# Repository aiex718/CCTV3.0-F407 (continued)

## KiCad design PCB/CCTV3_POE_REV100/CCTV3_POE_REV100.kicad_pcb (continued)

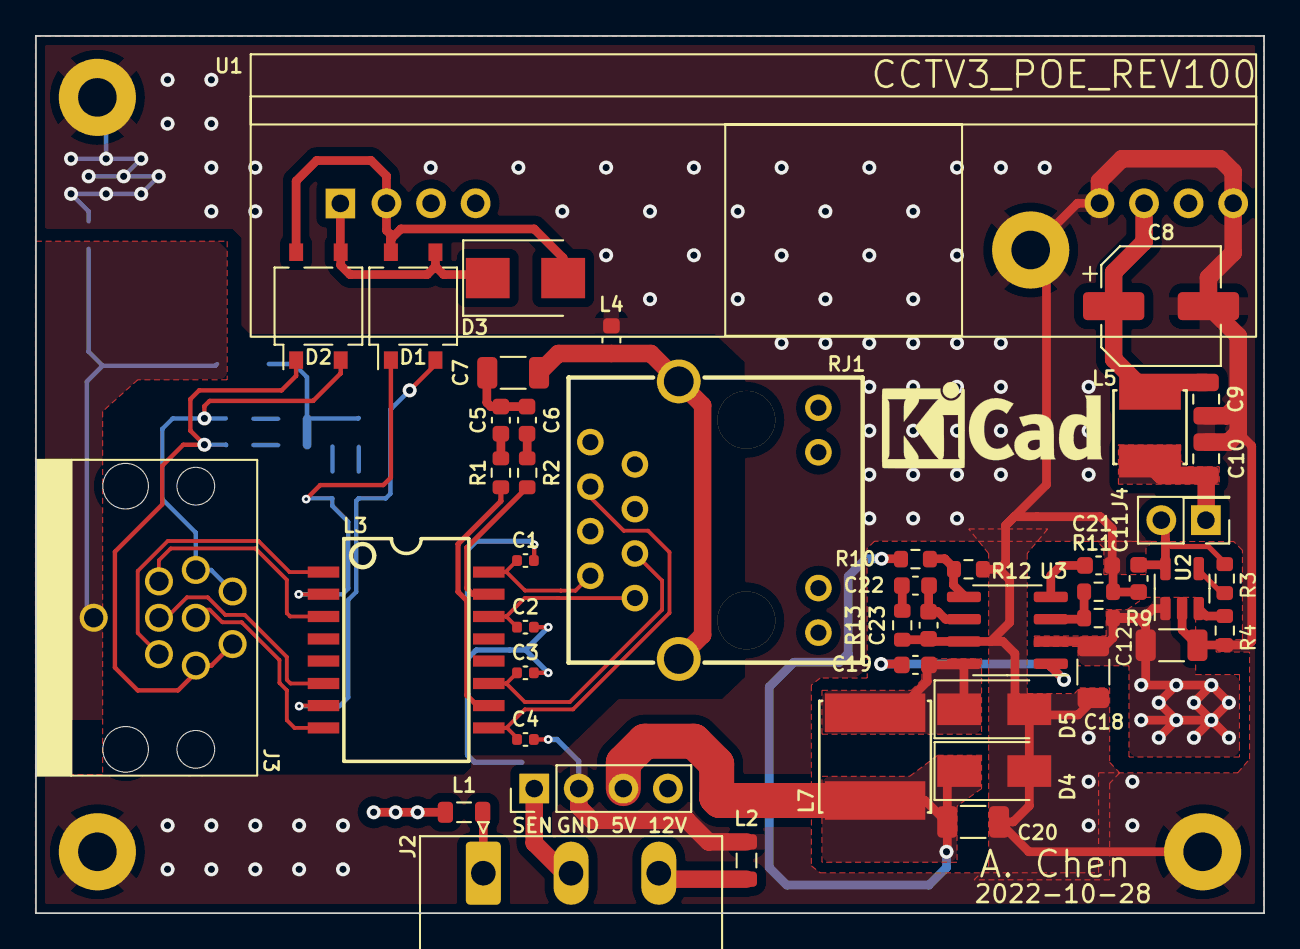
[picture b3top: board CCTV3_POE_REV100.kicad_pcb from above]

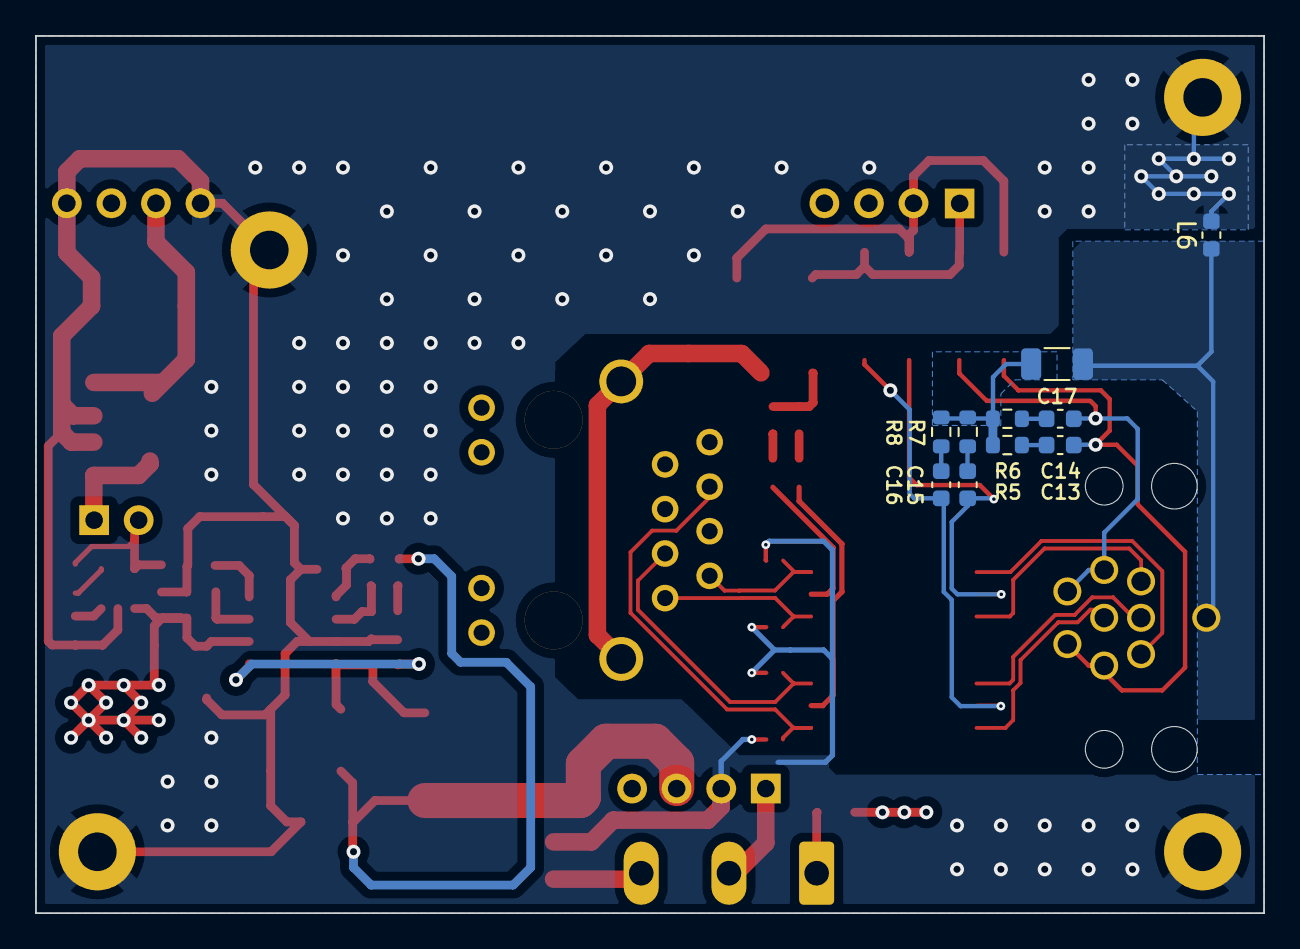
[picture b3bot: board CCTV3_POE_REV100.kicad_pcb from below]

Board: 4 copper layers, 70.0 x 50.0 mm, 60 parts (10 on the bottom side), 44 nets.

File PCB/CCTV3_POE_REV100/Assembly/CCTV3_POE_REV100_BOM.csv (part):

"Source:","/Users/aiex718/Private/Workspace/CCTV3.0-F407/PCB/CCTV3_POE_REV100/CCTV3_POE_REV100.kicad_sch"
"Date:","Thursday, 24 November 2022 at 03:23:11"
"Tool:","Eeschema (6.0.8-1)-1"
"Generator:","/Applications/KiCad/KiCad.app/Contents/SharedSupport/plugins/bom_csv_grouped_by_value.py"
"Component Count:","60"

"Individual Components:"

"Item","Qty","Reference(s)","Value","LibPart","Footprint","Datasheet","JLC Part","LCSC Part","Manufacturer","Model","Voltage"
"","","C1","10pF","lcsc_parts:Cap","Capacitor_SMD:C_0402_1005Metric","~","","TBD","","","50V"
"","","C2","10pF","lcsc_parts:Cap","Capacitor_SMD:C_0402_1005Metric","~","","TBD","","","50V"
"","","C3","10pF","lcsc_parts:Cap","Capacitor_SMD:C_0402_1005Metric","~","","TBD","","","50V"
"","","C4","10pF","lcsc_parts:Cap","Capacitor_SMD:C_0402_1005Metric","~","","TBD","","","50V"
"","","C5","10nF","lcsc_parts:Cap","Capacitor_SMD:C_0603_1608Metric","~","","TBD","","","250V"
"","","C6","10nF","lcsc_parts:Cap","Capacitor_SMD:C_0603_1608Metric","~","","TBD","","","250V"
"","","C7","1000pF","lcsc_parts:Cap","Capacitor_SMD:C_1206_3216Metric","~","","TBD","","","2KV"
"","","C8","220uF","lcsc_parts:Cap_Polarized","Capacitor_SMD:CP_Elec_6.3x7.7","https://lcsc.com/product-detail/Others_Lelon-VZT221M1ETR-060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","Extended Part","C371974","Lelon","","25V"
"","","C9","10uF","lcsc_parts:Cap","Capacitor_SMD:C_0805_2012Metric","~","","TBD","","","25V"
"","","C10","10uF","lcsc_parts:Cap","Capacitor_SMD:C_0805_2012Metric","~","","TBD","","","25V"
"","","C11","10uF","lcsc_parts:Cap","Capacitor_SMD:C_0603_1608Metric","~","","TBD","","","25V"
"","","C12","10uF","lcsc_parts:Cap","Capacitor_SMD:C_1206_3216Metric","~","","TBD","","","50V"
"","","C13","10nF","lcsc_parts:Cap","Capacitor_SMD:C_0603_1608Metric","~","","TBD","","","250V"
"","","C14","10nF","lcsc_parts:Cap","Capacitor_SMD:C_0603_1608Metric","~","","TBD","","","250V"
"","","C15","10nF","lcsc_parts:Cap","Capacitor_SMD:C_0603_1608Metric","~","","TBD","","","250V"
"","","C16","10nF","lcsc_parts:Cap","Capacitor_SMD:C_0603_1608Metric","~","","TBD","","","250V"
"","","C17","1000pF","lcsc_parts:Cap","Capacitor_SMD:C_1206_3216Metric","~","","TBD","","","2KV"
"","","C18","10uF","lcsc_parts:Cap","Capacitor_SMD:C_1206_3216Metric","~","","TBD","","","50V"
"","","C19","100nF","lcsc_parts:Cap","Capacitor_SMD:C_0603_1608Metric","~","","TBD","","","50V"
"","","C20","47uF","lcsc_parts:Cap","Capacitor_SMD:C_1206_3216Metric","~","","TBD","","","10V"
"","","C21","10nF","lcsc_parts:Cap","Capacitor_SMD:C_0603_1608Metric","~","","TBD","","","50"
"","","C22","1nF","lcsc_parts:Cap","Capacitor_SMD:C_0603_1608Metric","~","","TBD","","","50V"
"","","C23","47pF","lcsc_parts:Cap","Capacitor_SMD:C_0603_1608Metric","~","","TBD","","","50V"
"","","D1","MB6S","Diode_Bridge:MB6S","Package_TO_SOT_SMD:TO-269AA","http://www.vishay.com/docs/88573/dfs.pdf","","","","",""
"","","D2","MB6S","Diode_Bridge:MB6S","Package_TO_SOT_SMD:TO-269AA","http://www.vishay.com/docs/88573/dfs.pdf","","","","",""
"","","D3","SMBJ58A","lcsc_parts:SMBJ58A_C707476","Diode_SMD:D_SMB","https://lcsc.com/product-detail/TVS_FTR-SMBJ58A_C707476.html","Extended Part","C707476","FTR","",""
"","","D4","SMAJ5.0CA","lcsc_parts:SMAJ5.0CA-C83324","Diode_SMD:D_SMA","https://lcsc.com/product-detail/TVS_Littelfuse_SMAJ5-0CA_SMA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","Extended Part","C83324","Littelfuse","",""
"","","D5","SS34","lcsc_parts:SS34","Diode_SMD:D_SMA","https://lcsc.com/product-detail/Schottky-Barrier-Diodes-SBD_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","Basic Part","C8678","MDD","",""
"","","H1","MountingHole","Mechanical:MountingHole_Pad","MountingHole:MountingHole_2.2mm_M2_Pad","~","","","","",""
"","","H2","MountingHole","Mechanical:MountingHole_Pad","MountingHole:MountingHole_2.2mm_M2_Pad","~","","","","",""
"","","H3","MountingHole","Mechanical:MountingHole_Pad","MountingHole:MountingHole_2.2mm_M2_Pad","~","","","","",""
"","","H4","MountingHole","Mechanical:MountingHole_Pad","MountingHole:MountingHole_2.2mm_M2_Pad","~","","","","",""
"","","J1","Conn_01x04","Connector_Generic:Conn_01x04","Connector_PinHeader_2.54mm:PinHeader_1x04_P2.54mm_Vertical","~","","","","",""
"","","J2","Conn_4-20mA","Connector_Generic:Conn_01x03","Connector_Phoenix_MSTB:PhoenixContact_MSTBA_2,5_3-G_1x03_P5.00mm_Horizontal","~","","","","",""
"","","J3","M12_8P_Horizontal","CCTV3_POE:M12_8P_Horizontal","CCTV3_POE:M12_8P_Horizontal","https://item.taobao.com/item.htm?spm=a230r.1.14.231.1cd43c38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","","","","",""
"","","J4","Jmp_12V","Connector_Generic:Conn_01x02","Connector_PinHeader_2.54mm:PinHeader_2x01_P2.54mm_Vertical","~","","","","",""
"","","L1","100R","lcsc_parts:GZ1608D601TF","Inductor_SMD:L_0805_2012Metric","https://lcsc.com/product-detail/Ferrite-Beads-And-Chips_600R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","Basic Part","C1015","Sunlord","GZ2012D101TF",""
"","","L2","100R","lcsc_parts:GZ1608D601TF","Inductor_SMD:L_0805_2012Metric","https://lcsc.com/product-detail/Ferrite-Beads-And-Chips_600R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","Basic Part","C1015","Sunlord","GZ2012D101TF",""
"","","L3","HY601742","lcsc_parts:HY601742","lcsc_parts:RJ45-SMD_HY601742","https://lcsc.com/product-detail/RJ45-Transformer_100MNetwork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","Extended Part","C55684","HANRUN","",""
"","","L4","600R","lcsc_parts:GZ1608D601TF","Inductor_SMD:L_0603_1608Metric","https://lcsc.com/product-detail/Ferrite-Beads-And-Chips_600R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","Basic Part","C1002","Sunlord","GZ1608D601TF",""
"","","L5","SMNR4020-2.2UH","lcsc_parts:SMNR4020-2.2UH","lcsc_parts:IND-SMD_L4.0-W4.0_SMNR4020","https://lcsc.com/product-detail/Power-Inductors_2-2uH-20_C13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","Extended Part","C135262","SXN","",""
"","","L6","600R","lcsc_parts:GZ1608D601TF","Inductor_SMD:L_0603_1608Metric","https://lcsc.com/product-detail/Ferrite-Beads-And-Chips_600R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","Basic Part","C1002","Sunlord","GZ1608D601TF",""
"","","L7","33uH","lcsc_parts:LVS606045-330M-N","lcsc_parts:IND-SMD_L6.0-W6.0","https://lcsc.com/product-detail/Power-Inductors_Chilisin-Ele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","","C285825","Chilisin Elec","",""
"","","R1","75R","lcsc_parts:Res","Resistor_SMD:R_0603_1608Metric","~","","TBD","","",""
"","","R2","75R","lcsc_parts:Res","Resistor_SMD:R_0603_1608Metric","~","","TBD","","",""
"","","R3","4.7k","lcsc_parts:Res","Resistor_SMD:R_0603_1608Metric","~","","TBD","","",""
"","","R4","6.8k","lcsc_parts:Res","Resistor_SMD:R_0603_1608Metric","~","","TBD","","",""
"","","R5","75R","lcsc_parts:Res","Resistor_SMD:R_0603_1608Metric","~","","TBD","","",""
"","","R6","75R","lcsc_parts:Res","Resistor_SMD:R_0603_1608Metric","~","","TBD","","",""
"","","R7","75R","lcsc_parts:Res","Resistor_SMD:R_0603_1608Metric","~","","TBD","","",""
"","","R8","75R","lcsc_parts:Res","Resistor_SMD:R_0603_1608Metric","~","","TBD","","",""
"","","R9","330k","lcsc_parts:Res","Resistor_SMD:R_0603_1608Metric","~","","TBD","","",""
"","","R10","10k","lcsc_parts:Res","Resistor_SMD:R_0603_1608Metric","~","","TBD","","",""
"","","R11","68k","lcsc_parts:Res","Resistor_SMD:R_0603_1608Metric","~","","TBD","","",""
"","","R12","2k","lcsc_parts:Res","Resistor_SMD:R_0603_1608Metric","~","","TBD","","",""
"","","R13","30K","lcsc_parts:Res","Resistor_SMD:R_0603_1608Metric","~","","TBD","","",""
"","","RJ1","R-RJ45S08P-C000","lcsc_parts:R-RJ45S08P-C000","lcsc_parts:RJ45-TH_R-RJ45S08P-C000","https://lcsc.com/product-detail/Ethernet-Connectors-Modular-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","Extended Part","C386764","Shenzhen Cankemeng","",""
"","","U1","DP5312_SDAPO","CCTV3_POE:DP5312_SDAPO","CCTV3_POE:DP5312_SDAPO","","","","","",""
"","","U2","MT9700","lcsc_parts:MT9700","Package_TO_SOT_SMD:SOT-23-5","https://lcsc.com/product-detail/PMIC-Power-Distribution-Swit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","Extended Part","C89855","AEROSEMI","",""
"","","U3","TPS54331DR","lcsc_parts:TPS54331DR","Package_SO:SOIC-8_3.9x4.9mm_P1.27mm","https://lcsc.com/product-detail/DC-DC-Converters_TI_TPS54331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","Basic Part","C9865","TI","",""



"Collated Components:"

"Item","Qty","Reference(s)","Value","LibPart","Footprint","Datasheet","JLC Part","LCSC Part","Manufacturer","Model","Voltage"
"1","4","C1, C2, C3, C4","10pF","lcsc_parts:Cap","Capacitor_SMD:C_0402_1005Metric","~","","TBD","","","50V"
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
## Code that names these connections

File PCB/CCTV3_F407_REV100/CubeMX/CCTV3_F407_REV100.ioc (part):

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Mcu.Name=STM32F407Z(E-G)Tx
Mcu.Package=LQFP144
Mcu.UserName=STM32F407ZETx
PA0-WKUP.GPIOParameters=GPIO_Label
PA0-WKUP.GPIO_Label=BTN_WKUP
PA0-WKUP.Signal=GPIO_Input
PA1.Mode=RMII
PA1.Signal=ETH_REF_CLK
PA10.GPIOParameters=GPIO_Label
PA10.GPIO_Label=USB_OTG_FS_ID
PA10.Signal=GPIO_Output
PA11.Mode=Device_Only
PA11.Signal=USB_OTG_FS_DM
PA12.Mode=Device_Only
PA12.Signal=USB_OTG_FS_DP
PA13.Mode=JTAG_5_pins
PA13.Signal=SYS_JTMS-SWDIO
PA14.Mode=JTAG_5_pins
PA14.Signal=SYS_JTCK-SWCLK
PA15.Mode=JTAG_5_pins
PA15.Signal=SYS_JTDI
PA2.Mode=RMII
PA2.Signal=ETH_MDIO
PA3.Signal=ADCx_IN3
PA4.Mode=Slave_8_bits_External_Synchro
PA4.Signal=DCMI_HSYNC
PA6.Mode=Slave_8_bits_External_Synchro
PA6.Signal=DCMI_PIXCLK
PA7.Mode=RMII
PA7.Signal=ETH_CRS_DV
PA8.Mode=Clock-out-1
PA8.Signal=RCC_MCO_1
PA9.Mode=Slave_8_bits_External_Synchro
PA9.Signal=DCMI_D0
PB0.GPIOParameters=GPIO_Label
PB0.GPIO_Label=PWM_NC0
PB0.Signal=S_TIM3_CH3
PB1.GPIOParameters=GPIO_Label
PB1.GPIO_Label=PWM_NC1
PB1.Signal=S_TIM3_CH4
PB10.Mode=I2C
PB10.Signal=I2C2_SCL
PB11.Mode=I2C
PB11.Signal=I2C2_SDA
PB12.Mode=NSS_Signal_Hard_Input
PB12.Signal=SPI2_NSS
PB13.Mode=Full_Duplex_Master
PB13.Signal=SPI2_SCK
PB14.Mode=Full_Duplex_Master
PB14.Signal=SPI2_MISO
PB15.Mode=Full_Duplex_Master
PB15.Signal=SPI2_MOSI
PB2.GPIOParameters=GPIO_Label
PB2.GPIO_Label=BOOT1
PB2.Signal=GPIO_Input
PB3.Mode=JTAG_5_pins
PB3.Signal=SYS_JTDO-SWO
PB4.Mode=JTAG_5_pins
PB4.Signal=SYS_JTRST
PB5.GPIOParameters=GPIO_Label
PB5.GPIO_Label=PWM_NC2
PB5.Signal=S_TIM3_CH2
PB6.Mode=Slave_8_bits_External_Synchro
PB6.Signal=DCMI_D5
PB7.Mode=Slave_8_bits_External_Synchro
PB7.Signal=DCMI_VSYNC
PB8.GPIOParameters=GPIO_Label
PB8.GPIO_Label=SCCB_SCL
PB8.Mode=I2C
PB8.Signal=I2C1_SCL
PB9.GPIOParameters=GPIO_Label
PB9.GPIO_Label=SCCB_SDA
PB9.Mode=I2C
PB9.Signal=I2C1_SDA
PC1.Mode=RMII
PC1.Signal=ETH_MDC
PC10.Mode=Asynchronous
PC10.Signal=USART3_TX
PC11.Mode=Asynchronous
PC11.Signal=USART3_RX
PC12.Mode=Asynchronous
PC12.Signal=UART5_TX
PC13-ANTI_TAMP.GPIOParameters=GPIO_Label
PC13-ANTI_TAMP.GPIO_Label=BTN_TAMP
PC13-ANTI_TAMP.Signal=GPIO_Input
PC14-OSC32_IN.Mode=LSE-External-Oscillator
PC14-OSC32_IN.Signal=RCC_OSC32_IN
PC15-OSC32_OUT.Mode=LSE-External-Oscillator
PC15-OSC32_OUT.Signal=RCC_OSC32_OUT
PC4.Mode=RMII
PC4.Signal=ETH_RXD0
PC5.Mode=RMII
PC5.Signal=ETH_RXD1
PC6.GPIOParameters=GPIO_Label
PC6.GPIO_Label=PWM_NC3
PC6.Signal=S_TIM3_CH1
PC7.Mode=Slave_8_bits_External_Synchro
PC7.Signal=DCMI_D1
PC8.Mode=Slave_8_bits_External_Synchro
PC8.Signal=DCMI_D2
PC9.Mode=Slave_8_bits_External_Synchro
PC9.Signal=DCMI_D3
PD0.Signal=FSMC_D2_DA2
PD1.Signal=FSMC_D3_DA3
PD10.Signal=FSMC_D15_DA15
PD11.Signal=FSMC_A16_CLE
PD12.Signal=FSMC_A17_ALE
PD14.Signal=FSMC_D0_DA0
PD15.Signal=FSMC_D1_DA1
PD2.Mode=Asynchronous
PD2.Signal=UART5_RX
PD4.Signal=FSMC_NOE
PD5.Signal=FSMC_NWE
PD8.Signal=FSMC_D13_DA13
PD9.Signal=FSMC_D14_DA14
PE0.Signal=FSMC_NBL0
PE1.Signal=FSMC_NBL1
PE10.Signal=FSMC_D7_DA7
PE11.Signal=FSMC_D8_DA8
PE12.Signal=FSMC_D9_DA9
PE13.Signal=FSMC_D10_DA10
PE14.Signal=FSMC_D11_DA11
PE15.Signal=FSMC_D12_DA12
PE2.GPIOParameters=GPIO_Label
PE2.GPIO_Label=OV_PWDN
PE2.Signal=GPIO_Output
PE3.GPIOParameters=GPIO_Label
PE3.GPIO_Label=OV_RESET
PE3.Signal=GPIO_Output
PE4.Mode=Slave_8_bits_External_Synchro
PE4.Signal=DCMI_D4
PE5.Mode=Slave_8_bits_External_Synchro
PE5.Signal=DCMI_D6
PE6.Mode=Slave_8_bits_External_Synchro
PE6.Signal=DCMI_D7
PE7.Signal=FSMC_D4_DA4
PE8.Signal=FSMC_D5_DA5
PE9.Signal=FSMC_D6_DA6
PF0.Signal=FSMC_A0
PF1.Signal=FSMC_A1
PF11.GPIOParameters=GPIO_Label
PF11.GPIO_Label=LED_LINK
PF11.Signal=GPIO_Output
PF12.Signal=FSMC_A6
PF13.Signal=FSMC_A7
PF14.Signal=FSMC_A8
PF15.Signal=FSMC_A9
PF2.Signal=FSMC_A2
PF3.Signal=FSMC_A3
PF4.Signal=FSMC_A4
PF5.Signal=FSMC_A5
PF6.GPIOParameters=GPIO_Label
PF6.GPIO_Label=BUZZ_OUT
PF6.Signal=S_TIM10_CH1
PF7.GPIOParameters=GPIO_Label
PF7.GPIO_Label=LED_PWM_CH1
PF7.Signal=S_TIM11_CH1
PF8.GPIOParameters=GPIO_Label
PF8.GPIO_Label=LED_PWM_CH2
PF8.Signal=S_TIM13_CH1
PG0.Signal=FSMC_A10
PG1.Signal=FSMC_A11
PG11.Mode=RMII
PG11.Signal=ETH_TX_EN
PG12.Mode=NorPsramChipSelect4_1
PG12.Signal=FSMC_NE4
PG13.Mode=RMII
PG13.Signal=ETH_TXD0
PG14.Mode=RMII
PG14.Signal=ETH_TXD1
PG15.GPIOParameters=GPIO_Label
PG15.GPIO_Label=LED_STAT
PG15.Signal=GPIO_Output
PG2.Signal=FSMC_A12
PG3.Signal=FSMC_A13
PG4.Signal=FSMC_A14
PG5.Signal=FSMC_A15
PH0-OSC_IN.Mode=HSE-External-Oscillator
PH0-OSC_IN.Signal=RCC_OSC_IN
PH1-OSC_OUT.Mode=HSE-External-Oscillator
PH1-OSC_OUT.Signal=RCC_OSC_OUT
RCC.HSE_VALUE=25000000
RCC.SYSCLKFreq_VALUE=168000000
RCC.SYSCLKSource=RCC_SYSCLKSOURCE_PLLCLK
board=custom

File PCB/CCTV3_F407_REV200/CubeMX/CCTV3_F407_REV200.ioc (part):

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Mcu.Name=STM32F407V(E-G)Tx
Mcu.Package=LQFP100
Mcu.UserName=STM32F407VETx
PA0-WKUP.GPIOParameters=GPIO_Label
PA0-WKUP.GPIO_Label=BTN_WKUP
PA0-WKUP.Signal=GPIO_Input
PA1.Mode=RMII
PA1.Signal=ETH_REF_CLK
PA10.GPIOParameters=GPIO_Label
PA10.GPIO_Label=USB_OTG_FS_ID
PA10.Signal=GPIO_Input
PA11.Mode=Device_Only
PA11.Signal=USB_OTG_FS_DM
PA12.Mode=Device_Only
PA12.Signal=USB_OTG_FS_DP
PA13.Mode=Serial_Wire
PA13.Signal=SYS_JTMS-SWDIO
PA14.Mode=Serial_Wire
PA14.Signal=SYS_JTCK-SWCLK
PA15.GPIOParameters=GPIO_Label
PA15.GPIO_Label=W25_CS
PA15.Mode=NSS_Signal_Hard_Output
PA15.Signal=SPI3_NSS
PA2.Mode=RMII
PA2.Signal=ETH_MDIO
PA3.GPIOParameters=GPIO_Label
PA3.GPIO_Label=PWM_BUZZ
PA3.Signal=S_TIM9_CH2
PA4.Mode=Slave_8_bits_External_Synchro
PA4.Signal=DCMI_HSYNC
PA6.Mode=Slave_8_bits_External_Synchro
PA6.Signal=DCMI_PIXCLK
PA7.Mode=RMII
PA7.Signal=ETH_CRS_DV
PA8.Mode=Clock-out-1
PA8.Signal=RCC_MCO_1
PB11.Mode=RMII
PB11.Signal=ETH_TX_EN
PB12.Mode=RMII
PB12.Signal=ETH_TXD0
PB13.Mode=RMII
PB13.Signal=ETH_TXD1
PB14.GPIOParameters=GPIO_Label
PB14.GPIO_Label=PWM_LED_CH1
PB14.Signal=S_TIM12_CH1
PB15.GPIOParameters=GPIO_Label
PB15.GPIO_Label=PWM_LED_CH2
PB15.Signal=S_TIM12_CH2
PB2.GPIOParameters=GPIO_Label
PB2.GPIO_Label=BOOT1
PB2.Signal=GPIO_Input
PB6.Mode=Slave_8_bits_External_Synchro
PB6.Signal=DCMI_D5
PB7.Mode=Slave_8_bits_External_Synchro
PB7.Signal=DCMI_VSYNC
PB8.GPIOParameters=GPIO_Label
PB8.GPIO_Label=SCCB_SCL
PB8.Mode=I2C
PB8.Signal=I2C1_SCL
PB9.GPIOParameters=GPIO_Label
PB9.GPIO_Label=SCCB_SDA
PB9.Mode=I2C
PB9.Signal=I2C1_SDA
PC0.GPIOParameters=GPIO_Label
PC0.GPIO_Label=LED_LOAD
PC0.Signal=GPIO_Output
PC1.Mode=RMII
PC1.Signal=ETH_MDC
PC10.GPIOParameters=GPIO_Label
PC10.GPIO_Label=W25_SCK
PC10.Mode=Full_Duplex_Master
PC10.Signal=SPI3_SCK
PC11.GPIOParameters=GPIO_Label
PC11.GPIO_Label=W25_MISO
PC11.Mode=Full_Duplex_Master
PC11.Signal=SPI3_MISO
PC12.GPIOParameters=GPIO_Label
PC12.GPIO_Label=W25_MOSI
PC12.Mode=Full_Duplex_Master
PC12.Signal=SPI3_MOSI
PC13-ANTI_TAMP.GPIOParameters=GPIO_Label
PC13-ANTI_TAMP.GPIO_Label=BTN_TAMP
PC13-ANTI_TAMP.Signal=GPIO_Input
PC14-OSC32_IN.Mode=LSE-External-Oscillator
PC14-OSC32_IN.Signal=RCC_OSC32_IN
PC15-OSC32_OUT.Mode=LSE-External-Oscillator
PC15-OSC32_OUT.Signal=RCC_OSC32_OUT
PC2.GPIOParameters=GPIO_Label
PC2.GPIO_Label=LED_STAT
PC2.Signal=GPIO_Output
PC3.Signal=ADCx_IN13
PC4.Mode=RMII
PC4.Signal=ETH_RXD0
PC5.Mode=RMII
PC5.Signal=ETH_RXD1
PC6.Mode=Slave_8_bits_External_Synchro
PC6.Signal=DCMI_D0
PC7.Mode=Slave_8_bits_External_Synchro
PC7.Signal=DCMI_D1
PC9.Mode=Clock-out-2
PC9.Signal=RCC_MCO_2
PD8.Mode=Asynchronous
PD8.Signal=USART3_TX
PD9.Mode=Asynchronous
PD9.Signal=USART3_RX
PE0.Mode=Slave_8_bits_External_Synchro
PE0.Signal=DCMI_D2
PE1.Mode=Slave_8_bits_External_Synchro
PE1.Signal=DCMI_D3
PE2.GPIOParameters=GPIO_Label
PE2.GPIO_Label=OV_PWDN
PE2.Signal=GPIO_Output
PE3.GPIOParameters=GPIO_Label
PE3.GPIO_Label=OV_RESET
PE3.Signal=GPIO_Output
PE4.Mode=Slave_8_bits_External_Synchro
PE4.Signal=DCMI_D4
PE5.Mode=Slave_8_bits_External_Synchro
PE5.Signal=DCMI_D6
PE6.Mode=Slave_8_bits_External_Synchro
PE6.Signal=DCMI_D7
PH0-OSC_IN.Mode=HSE-External-Oscillator
PH0-OSC_IN.Signal=RCC_OSC_IN
PH1-OSC_OUT.Mode=HSE-External-Oscillator
PH1-OSC_OUT.Signal=RCC_OSC_OUT
RCC.HSE_VALUE=25000000
RCC.SYSCLKFreq_VALUE=168000000
RCC.SYSCLKSource=RCC_SYSCLKSOURCE_PLLCLK
board=custom

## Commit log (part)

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2023-03-06 Init push.
2023-03-06 add CCTV3_POE_REV100
2023-03-06 Add CCTV3_F407_REV100
2023-03-06 Add mjpeg_bin note
2023-03-06 Add MDK_REV200, helloworld uart.
2023-03-07 Export pdf for F407_REV200
2023-03-24 Usart3 hello world interrupt, init ver.
2023-03-25 Usart3 stream mode with callback test.
2023-03-25 Move unit test folder
2023-03-25 Add test project BSP-USART3-Stream-Mode
2023-03-26 Fix rcc clock frequency, adjust systick priority to highest.
2023-03-26 Implement DMA init, deinit and cmd.
2023-03-26 Add bitflag
2023-03-26 USART use bitwise flag instead of callback pending queue to prevent duplicate callback. Change callback regist function.
2023-03-26 Edit main to adapt new callback function.
2023-03-26 Update BSP-USART-Stream-mode-test to use new callback regist function.
2023-03-26 Edit comment.
2023-03-28 update gitignore
2023-03-28 Buffer add Queue_IndexOf amd Queue_Remove fucntion.
2023-03-28 Rename stm32f4xx_it.c to sysirq.c ,move USART3_IRq from periph_list.c to sysirq.c
2023-03-28 Update buffer_test unit test to able to test IndexOf
2023-03-28 Add SysCtrl_SystemReset
2023-03-28 Fix wrong index type.
2023-03-28 Add configs.
2023-03-28 Implement DBG_Serial, can read line format cmd end with '\n'
2023-03-28 Remove uvoptx
2023-03-28 Update gitignore untrack uvoptx
2023-03-28 Update test BSP-USART3-DMA-Stream-Hybrid for renamed/moved file.
2023-03-28 Update test BSP-USART3-Stream-Mode for renamed/moved file.
2023-03-28 First BSP released. trimmed main, remove test project.
2023-03-28 Renamed test project
2023-03-28 Checkpoint
2023-03-30 Add Callback_InvokeIdx helper macro, add null check in Callback_Invoke macro
2023-03-30 Edit periph config for new implemented DMA
2023-03-30 Rename Usart Software to Polling, and other types
2023-03-30 Change macro to static inline function
2023-03-30 Rename invoke helper function to new format defined in callback.h.
2023-03-30 Adjust some USART IT_Config/IT_Clear order.
2023-03-30 Add back usart test project.
2023-03-30 Fix Stream mode stress command, now end with '\n'
2023-03-30 Fix BSP-USART3-DMA-Stream-Hybrid, add non-blocking fputc, will cause data loss when tx buffer full.
2023-03-30 Fix BSP-USART3-DebugSerial.
2023-04-01 Redo dma DMA_Stream_to_ITStatusFlags_Tbl
2023-04-01 Add usart comment.
2023-04-01 Implement MCO, not test yet.
2023-04-01 Implement I2C, not test yet.
2023-04-01 Fix mco include path.
2023-04-01 add comment for dma.
2023-04-01 Implement hardware timer.
2023-04-01 Implement timer_pwm based on timer
2023-04-01 Write a test for timer_pwm, prepare for a new branch for testing.
2023-04-01 Fix timer cmd pipeline issue.
2023-04-01 Implement device flashlight.
2023-04-01 Write test for FlashLight.
2023-04-01 Fix timer wrong nvic init code.
2023-04-01 Remove breathlight test code in main.
2023-04-01 Fix FlashLight-CH1-CH2 timer periph config wrong nvic and ITs.
2023-04-01 Fix BSP-Test main file caused by rename timer to systimer.
2023-04-01 Fix some omitted naming while rename timer to systimer.
2023-04-01 Fix some omitted naming while rename timer to systimer(refer to 604f0b2).
2023-04-04 Port lwip.
2023-04-04 rename memcpy to MEMCPY
2023-04-04 Implement webapi.
2023-04-05 Release file->pextension for dynamic read purpose, use file->data instead.
2023-04-05 Update vsocde include path for intellisense.
2023-04-05 Remove unused define.
2023-04-06 Edit attach logic, now only set pointer, move init part to Init function.
2023-04-06 Rename Device_FlashLight_Attach to Device_FlashLight_Attach_PWM
2023-04-19 ported mjpegd.
2023-04-19 implement dcmi for cam_ov2640.
2023-04-19 Rename and update configs.
2023-04-19 Update main for mjpeg and cam_ov2640
2023-04-19 Split ITs into 2 files, system_its.c and periph_its.c
2023-04-19 Rename DMA callbacks, modify ReloadCfg now will reset callbacks and it flags,
2023-04-19 Reimplement usart and dbg_serial , add comment,
2023-04-19 Separate startup.s from Lib
2023-04-19 add volatile to Bitflag
2023-04-19 edit callback func, now with owner attribute.
2023-04-19 change allow preemption to bool flag instead of #define ,add comment for concurrent_queue
2023-04-19 impl mem_utils
2023-04-19 add 2 unit test, semaphore_test and spinlock_test
2023-04-19 Update platform and periphs.
2023-04-19 remove stack_guard.h, not implemented.
2023-04-19 Remove comments
2023-04-19 change printf to DBG_INFO
2023-04-19 Add different DBG level.
2023-04-19 remove unused #define in cam_ov2640
2023-04-19 Add link change detection task to lwip timeout.
2023-04-19 Edit lwipopts.
2023-04-20 Rename mjpegd_macro.h to mjpegd_memutils.h
2023-04-20 remove fwdecl
2023-04-20 ImplementDevice_CamOV2640_SetBuf and Device_CamOV2640_SetQs, move frame_len from CAMOV2640_CALLBACK_NEWFRAME callback arg to self->CamOV2640_FrameBuf_Len.
2023-04-20 Add function Mjpegd_Frame_CaptureFinish Mjpegd_Frame_InsertComment
    Remove function
    Mjpegd_Frame_WriteComment
2023-04-20 Update mjpegd.c using various new function.
2023-04-20 Remove ordering in mjpegd_stream_output, rename function pointer.
2023-04-20 add mjpegd_typedef, for bridging bsp.
2023-04-20 fix comment.
2023-04-20 Move header/tail/eof const string to function local static var.
2023-04-20 use sys_now instead of SysTime_Get.
2023-04-20 Rename MJPEGD_STRLEN to MJPEGD_CHRARR_STRLEN(s)
2023-04-21 Refactor mjpegd, camera not implemented.
2023-04-21 Implement mjpegd_callback
2023-04-22 change semaphore implement.
2023-04-22 Implement mjpeg_camera
2023-04-22 Implement mjpegd_camera idle on/off, remove mjpegd_snap, related logic moved to mjpegd_stream.
2023-04-23 Implement dbg_usart_SafeMode
2023-04-23 Fix usart disable cmd dma not closed issue.
2023-04-23 Edit dbg_serial comment
2023-04-23 Change periph_list declaration style.
2023-04-23 Fix Default_SysFault_Loop.
2023-04-23 Export Stack_Mem for Mem_Guard
2023-04-24 Change payload_len to frame_len, original payload_len used for indicate plyload available len
2023-04-24 Move parse request to mjpegd_request.h Implement url params parser Implement fps limiter
2023-04-24 Edit options.
2023-04-24 Fix sio compile problem, still not implement.
2023-04-24 Rename #define in netconf.h
2023-04-24 Implement DHCP
2023-04-24 Fix debug function, edit options.
2023-04-24 Remove unused code.
2023-04-24 edit todo and comment, move options from netconf.h
2023-04-24 let DHCP not display ip when new lease received.
2023-04-24 set ip to 0 when disconnect rj45 cable.
2023-04-25 impl uniqueid.c/.h
2023-04-25 add periph_uniqueid
2023-04-25 Let camera wont show error when bad frame is expected.
2023-04-25 Implement DNS
2023-04-27 Impl rtc.
2023-04-27 Impl app nettime
2023-04-27 update vs setting
2023-04-27 Add clock and mco init function to rcc.c/.h Fix debug serial_cmd.
2023-04-27 Change struct naming style, use _s as struct name.
2023-04-27 Add rcc example, continue change name style.
2023-04-27 add rtc and nettime into main
2023-04-27 Change Frame insert comment implement, now support var length.
2023-04-27 remove forward decl in mjpegd.h
2023-04-27 edit view/fps to display unix epoch time.
2023-04-27 add sntp option, add GET_UNIX_TIMESTAMP define
2023-04-27 Rename FrameBuf to Frame Pool, change struct naming style for mjpeg.
2023-04-27 Apply new struct naming.
2023-04-27 Edit main
2023-04-27 Change peri head name.
2023-04-27 Seperate hal related instance to periph
2023-04-27 remove unused include
2023-04-27 move periph_list into sub folder, add platform_inst.h for include all instance.
2023-04-28 Move eth to bsp/
2023-04-28 Edit c_cpp_prop
2023-04-28 Edit include path and c_cpp_props.
2023-04-29 Remove vla, use #define static value instead.
2023-04-29 same as previous
2023-04-29 moved some opts.
2023-04-29 Make RCC_Init const.
2023-04-29 continue merge
2023-04-29 change mem_guard_init called position in main
2023-04-30 Remove LSE in RTC.
2023-04-30 Port nettime
2023-04-30 edit peri_rcc
2023-04-30 Improve rcc init routine
2023-04-30 Add flashlight and control.
2023-04-30 Fix include error
2023-04-30 Fix duplicate include
2023-05-02 Port lwip and device Flash_W25Qx.
2023-05-02 Port usbmsc.
2023-05-02 Port fat_fs, implement filesys.
2023-05-02 impl FileSys_GetLen
2023-05-02 Impl HTTP dynamic read for file not in fs_data.
2023-05-03 Move code rom to sector0 + sector 4 and onward.
2023-05-03 Update .gitignore allow .sct to be tracked
2023-05-03 Use custom sct file, move most of RW ZI to CCMRAM
2023-05-05 Fix BitFlag wrong macro.
2023-05-05 add math.h and BSP_ABS in platform defs.
2023-05-05 add DBG_PRINTF, rename original to DBG_PRINTF_LV
2023-05-05 Follow rename rcc
2023-05-05 rename peri_rcc.c
2023-05-05 Fix buf len not match
2023-05-05 Impl buzzer
2023-05-05 Add reset serial cmd
2023-05-05 Fix write byte polling.
2023-05-05 put more data into ccmram
2023-05-05 Remove unused systick in hal.
2023-05-05 put request_strreq into mjpeg_request.c
2023-05-05 raname buf
2023-05-05 Put usbd in CCMRAM
2023-05-09 Add BSP_RAND and BSP_MEMMOVE
2023-05-09 impl flash_prog and config_storage, no example in main, refer to config_storage.h for example usage.
2023-05-09 port fixed
2023-05-09 Change ethernetif.c , seperate config to config_file
2023-05-09 Change usart bitflag size.
2023-05-09 implement led_indicator and button
2023-05-09 Fix const error.
2023-05-09 Fix BitFlag
2023-05-09 Implement Mjpegd_Config
2023-05-09 Implement cam_ov2640_Config
2023-05-09 edit opts
2023-05-09 Fix Client_Closing error in Sent callback
2023-05-09 Try fix frame leak caused by DoSnap reentrant.
2023-05-09 Add dev_config_storage
2023-05-09 add file
2023-05-09 Apply stash
2023-05-10 Change some init code.
2023-05-10 rename dbg_serial safe_mode field, make sure all struct in bsp is mem align
2023-05-10 Remove unused file, checked mem aligned.
2023-05-10 Add back deleted file.
2023-05-10 Move some field for mem saving
2023-05-10 Fix mem align
2023-05-10 Adjust request instance.
2023-05-10 remove frame pool iscleared flag, adjust field order for better mem align.
2023-05-10 Add padding for mem align.
2023-05-10 Edit adc and val buf len.
2023-05-10 Use malloc for frame sorting.
2023-05-10 Use malloc instead of CONFIG_STORAGE_MAX_SIZE, write example config in .h
2023-05-10 Use BSP_ARR_CLEAR insdead of BSP_MEMSET for callback init.
2023-05-10 Remove unused code and duplidate define.
2023-05-10 Edit config for stress test
2023-05-10 add check for wbuf
2023-05-10 Edit mem_guard comment
2023-05-10 Remove set function for config_storage self, add function null check in load.
2023-05-10 Edit webapi.h
2023-05-10 edit vscode setting
2023-05-10 add library miniz for makefsdata.c
2023-05-10 add fsdata_custom.c
2023-05-11 Update web
2023-05-11 Move unnecessary code to .c
2023-05-11 fix undefined function
2023-05-11 add bootstrap.css
2023-05-11 edit debug output
2023-05-11 Update sysctrl
2023-05-11 impl http 404 and 503 response
2023-05-11 impl webhook
2023-05-11 change button long press period.
2023-05-11 Move callbacks to platform_callback.c
2023-05-11 Add SysCtrl_ResetAfter(ms)
2023-05-11 impl todo.
2023-05-11 Fix long press delay
2023-05-11 Fix private delc
2023-05-11 Edit comment
2023-05-11 Make fps counter dont print when camera disabled.
2023-05-11 Impl webhook api
2023-05-11 Fix webhook config is valid check
2023-05-11 Impl uartcmd, move code.
2023-05-11 fix include
2023-05-11 Fix wrong type
2023-05-12 Add reset api, clean some code.
2023-05-12 edit strcmp
2023-05-12 edit web, implement all webapi
2023-05-12 generate fsdata_custom for new website
2023-05-12 make current trig can be disable
2023-05-12 Edit isvalid check
2023-05-12 add option to not print open error
2023-05-12 Edit nettime config isvalid check
2023-05-12 use more ram
2023-05-13 Change webhook valid check
2023-05-13 Add random config generate function.
2023-05-13 Change padding, edit isvalid check logic
2023-05-13 Add raise hardfault func and dump stack.
2023-05-13 edit http_builder, now insert can limit max len.
2023-05-13 add a command to trigger hardfault.
2023-05-13 move adc init after lwip
2024-10-22 Add sch pdf
2024-10-22 Let buzzer beep when current trig
2024-10-22 Edit options
2024-11-03 Make CurrentTrig warning event info ourput configurable
2024-11-03 add 'help' command for uartcmd
2024-11-03 Print help message when init done
2024-11-03 change u8 to uint8_t
2024-11-05 add loopfreq command for uartcmd
2024-11-05 Add HAL_RCC_GetClockSpeed in HAL/RCC
2024-11-05 Fix usart tx dma mode bug
2024-11-05 Add PerfMon_StartMeasure and Stop in .h
2024-11-05 Fix usart dma issue
2024-11-05 add todo, edit platform_opt for new serial.c
